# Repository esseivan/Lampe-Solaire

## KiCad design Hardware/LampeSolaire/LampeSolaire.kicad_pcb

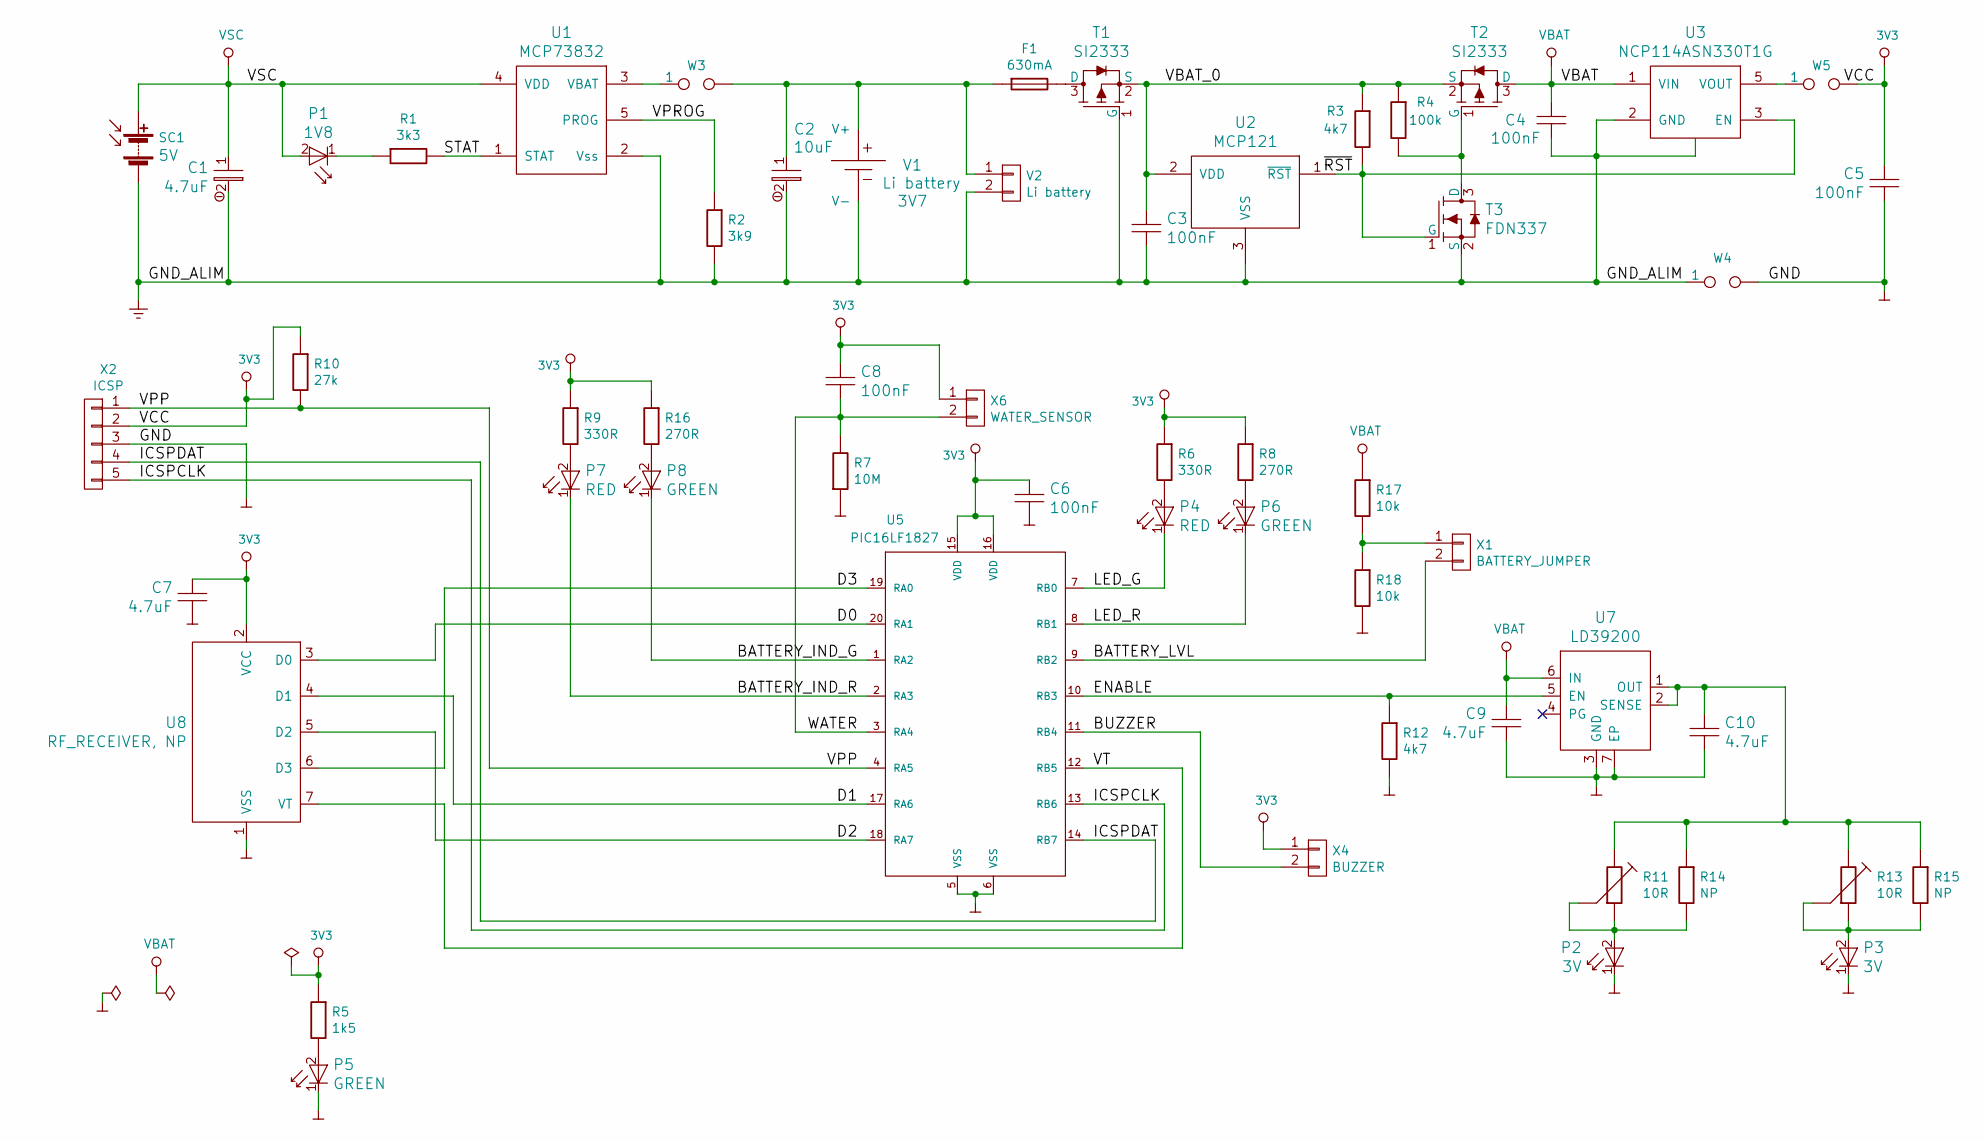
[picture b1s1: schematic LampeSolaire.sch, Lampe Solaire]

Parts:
C1, C7, C9, C10: 4.7uF; C_0805_HandSoldering
C2: 10uF; C_0805_HandSoldering
C3, C4, C5, C6, C8: 100nF; C_0805_HandSoldering
F1: 630mA; Fuse_SMD1206_HandSoldering
P1: 1V8; D_0603_HandSoldering
P2, P3: 3V; Pin_Header_Straight_1x02_Pitch2.54mm
P4, P7: RED; D_0603_HandSoldering
P5, P6, P8: GREEN; D_0603_HandSoldering
R1: 3k3; R_0805_HandSoldering
R2: 3k9; R_0805_HandSoldering
R3, R12: 4k7; R_0805_HandSoldering
R4: 100k; R_0805_HandSoldering
R5: 1k5; R_0805_HandSoldering
R6, R9: 330R; R_0805_HandSoldering
R7: 10M; R_0805_HandSoldering
R8, R16: 270R; R_0805_HandSoldering
R10: 27k; R_0805_HandSoldering
R11, R13: 10R; Potentiometer_Trimmer_Bourns_3006P
R14, R15: NP; R_0805_HandSoldering
R17, R18: 10k; R_0805_HandSoldering
SC1: Solar_Cells; Pin_Header_Straight_1x02_Pitch2.54mm; Voltage 5V
T1, T2: SI2333; SOT-23_Handsoldering
T3: FDN337; SOT-23_Handsoldering
U1: MCP73832; SOT-23-5_HandSoldering
U2: MCP121; SOT-23_Handsoldering
U3: NCP114ASN330T1G; TSOP-5
U5: PIC16LF1827; SSOP-20_5.3x7.2mm_Pitch0.65mm
U7: LD39200; DFN-6-1EP_3x3mm_Pitch0.95mm
U8: RF_RECEIVER, NP; RF_RECEIVER
V1: Li battery; 18650 Battery holder; Voltage 3V7
V2: Li battery; Pin_Header_Straight_1x02_Pitch2.54mm
W3, W4, W5: TEST_2P; Pin_Header_Straight_1x02_Pitch2.54mm
X1: BATTERY_JUMPER; Pin_Header_Straight_1x02_Pitch2.54mm
X2: ICSP; Pin_Header_Straight_1x05_Pitch2.54mm
X4: BUZZER; Pin_Header_Straight_1x02_Pitch2.54mm
X6: WATER_SENSOR; Pin_Header_Straight_1x02_Pitch2.54mm

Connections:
3V3: C5.1, C6.1, C7.1, C8.1, R5.2, R6.2, R8.2, R9.2, R10.2, R16.2, U5.15 (VDD), U5.16 (VDD), U8.2 (VCC), W5.2, X2.2, X4.1, X6.1
/BATTERY_IND_G: P8.1 (Cathode), U5.1 (RA2)
/BATTERY_IND_R: P7.1 (Cathode), U5.2 (RA3)
/BATTERY_LVL: U5.9 (RB2), X1.2
/BUZZER: U5.11 (RB4), X4.2
/D0: U5.20 (RA1), U8.3 (D0)
/D1: U5.17 (RA6), U8.4 (D1)
/D2: U5.18 (RA7), U8.5 (D2)
/D3: U5.19 (RA0), U8.6 (D3)
/ENABLE: R12.2, U5.10 (RB3), U7.5 (EN)
/ICSPCLK: U5.13 (RB6), X2.5
/ICSPDAT: U5.14 (RB7), X2.4
/LED_G: P4.1 (Cathode), U5.7 (RB0)
/LED_R: P6.1 (Cathode), U5.8 (RB1)
/STAT: R1.1, U1.1 (STAT)
/VBAT_0: C3.1, R3.2, R4.2, T1.2 (S), T2.2 (S), U2.2 (VDD)
/VPP: R10.1, U5.4 (RA5), X2.1
/VPROG: R2.2, U1.5 (PROG)
/VT: U5.12 (RB5), U8.7 (VT)
/WATER: C8.2, R7.1, U5.3 (RA4), X6.2
/~RST: R3.1, T3.1 (G), U2.1 (~RST), U3.3 (EN)
GND: C5.2, C6.2, C7.2, C9.2, C10.2, P2.1 (Cathode), P3.1 (Cathode), P5.1 (Cathode), R7.2, R12.1, R18.1, U5.5 (VSS), U5.6 (VSS), U7.3 (GND), U7.7 (EP), U8.1 (VSS), W4.2, X2.3
GND_ALIM: C1.2, C2.2, C3.2, C4.2, R2.1, SC1.2 (-), T1.1 (G), T3.2 (S), U1.2 (Vss), U2.3 (VSS), U3.2 (GND~), U3.4 (NC), V1.2 (V-), V2.2, W4.1
unnamed: C2.1, F1.2, V1.1 (V+), V2.1, W3.2
unnamed: C10.1, R11.1, R13.1, R14.2, R15.2, U7.1 (OUT), U7.2 (SENSE)
unnamed: F1.1, T1.3 (D)
unnamed: P1.1 (Cathode), R1.2
unnamed: P2.2 (Anode), R11.2, R11.3, R14.1
unnamed: P3.2 (Anode), R13.2, R13.3, R15.1
unnamed: P4.2 (Anode), R6.1
unnamed: P5.2 (Anode), R5.1
unnamed: P6.2 (Anode), R8.1
unnamed: P7.2 (Anode), R9.1
unnamed: P8.2 (Anode), R16.1
unnamed: R4.1, T2.1 (G), T3.3 (D)
unnamed: R17.1, R18.2, X1.1
unnamed: U1.3 (VBAT), W3.1
unnamed: U3.5 (VOUT), W5.1
VBAT: C4.1, C9.1, R17.2, T2.3 (D), U3.1 (VIN), U7.6 (IN)
VSC: C1.1, P1.2 (Anode), SC1.1 (+), U1.4 (VDD)

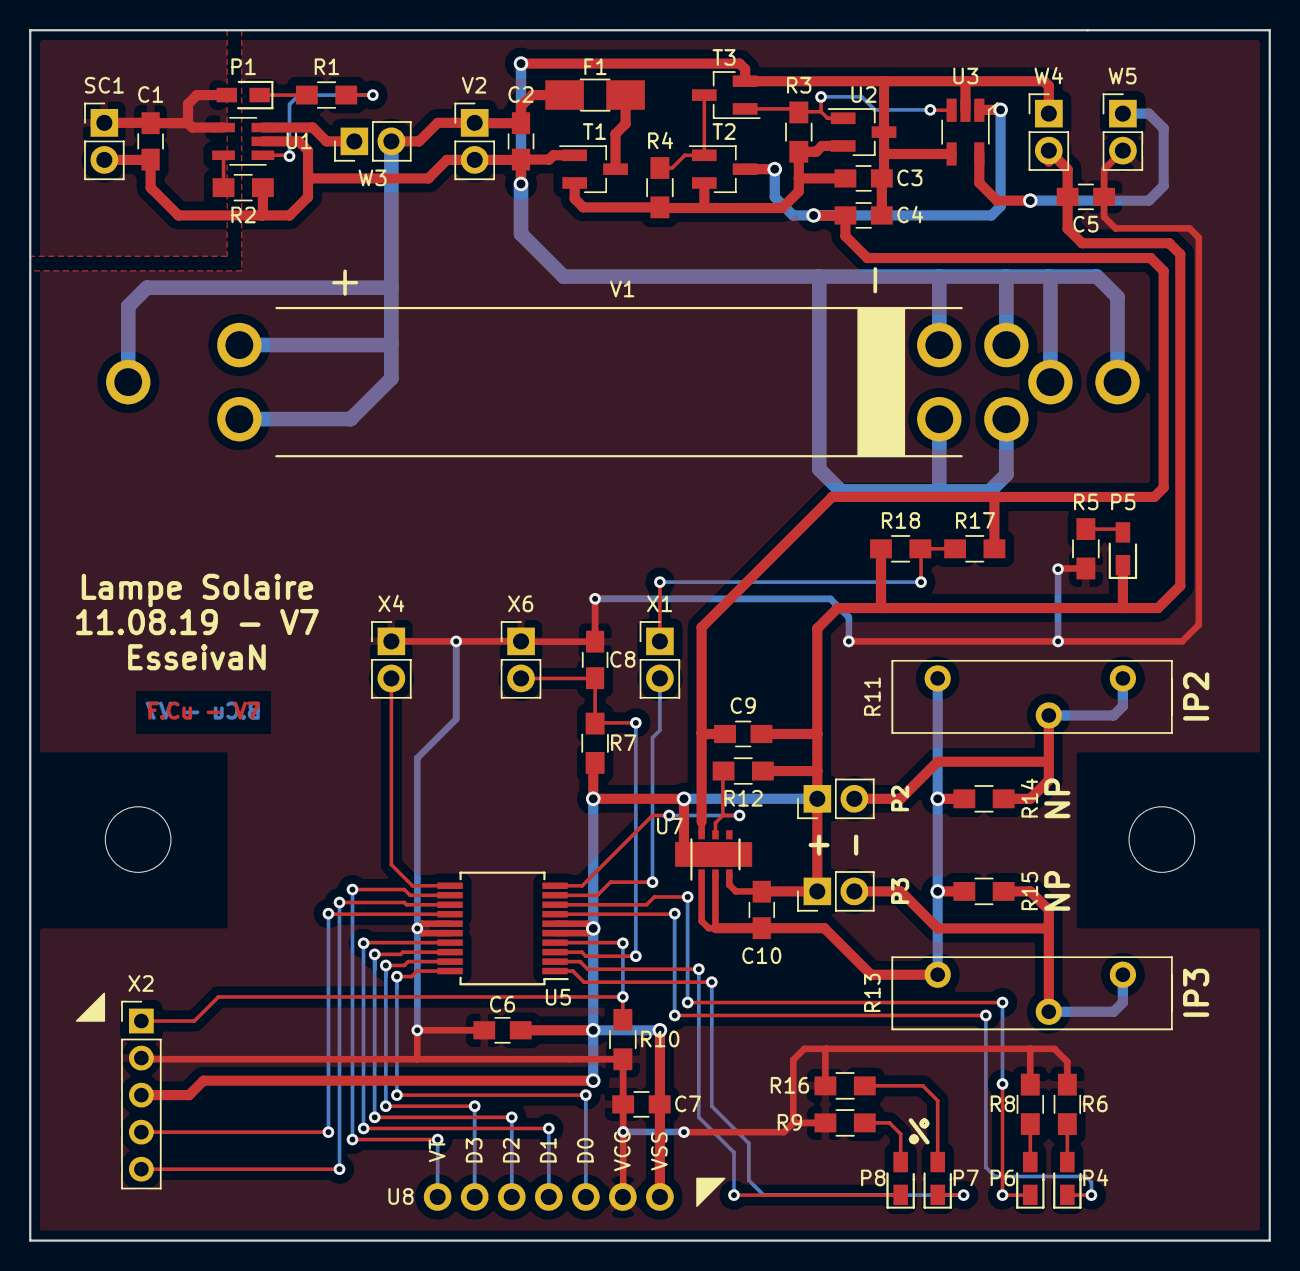
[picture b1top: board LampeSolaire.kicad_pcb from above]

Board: 2 copper layers, 85.0 x 83.0 mm, 58 parts (0 on the bottom side), 40 nets.

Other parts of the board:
PERC-4.5mm, PERC-4.5mm#2: PERC-4.5mm

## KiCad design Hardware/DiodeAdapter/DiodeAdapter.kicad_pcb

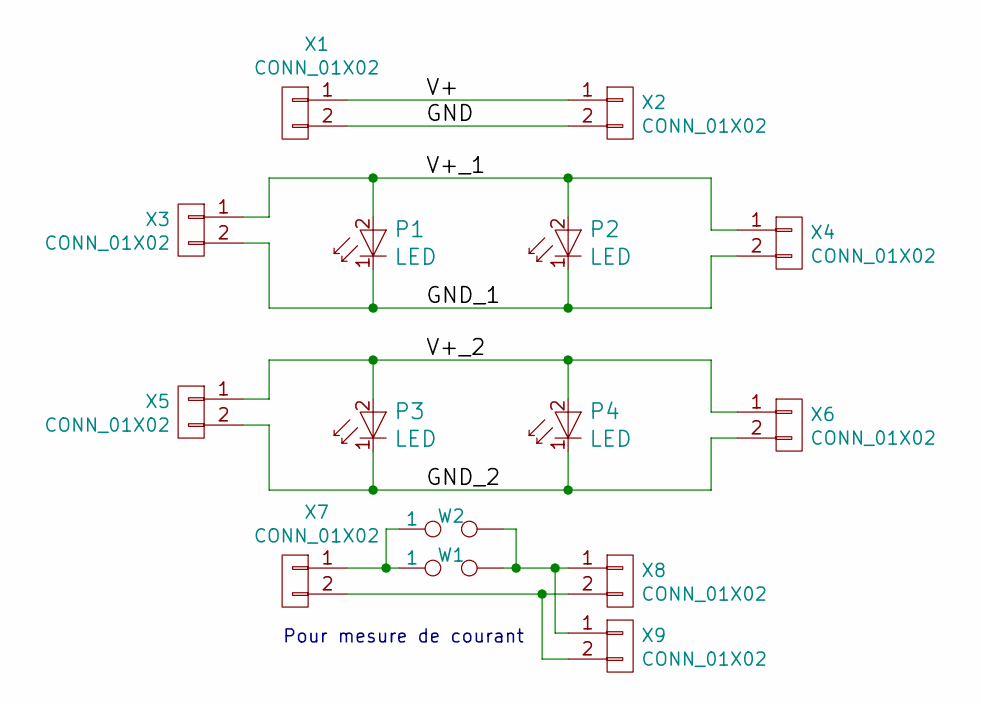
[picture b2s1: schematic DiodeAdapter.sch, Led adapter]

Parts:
P1, P3: LED; LED_LH351D
P2: LED; LED_LITTLE_STAR
P4: LED; LED_XQ_D
W1, W2: TEST_2P; Pin_Header_Straight_1x02_Pitch2.54mm
X1, X7: CONN_01X02; Pin_Header_Angled_1x02_Pitch2.54mm
X2, X3, X4, X5, X6, X9: CONN_01X02; Pin_Header_Straight_1x02_Pitch2.54mm
X8: CONN_01X02; Pin_Header_Angled_1x02_Pitch2.54mm_reverse

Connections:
/GND: X1.2, X2.2
/GND_1: P1.1 (Cathode), P2.1 (Cathode), X3.2, X4.2
/GND_2: P3.1 (Cathode), P4.1 (Cathode), X5.2, X6.2
/V+: X1.1, X2.1
/V+_1: P1.2 (Anode), P2.2 (Anode), X3.1, X4.1
/V+_2: P3.2 (Anode), P4.2 (Anode), X5.1, X6.1
unnamed: W1.1, W2.1, X7.1
unnamed: W1.2, W2.2, X8.1, X9.1
unnamed: X7.2, X8.2, X9.2

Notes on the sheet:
Pour mesure de courant

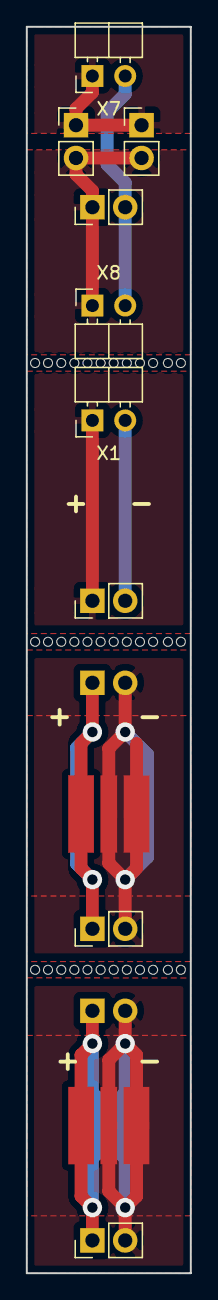
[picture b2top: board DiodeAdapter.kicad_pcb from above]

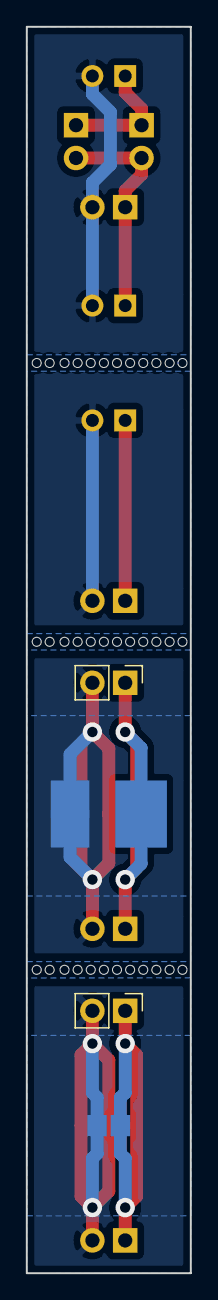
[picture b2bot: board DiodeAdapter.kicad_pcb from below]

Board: 2 copper layers, 12.7 x 96.5 mm, 15 parts (4 on the bottom side), 9 nets.

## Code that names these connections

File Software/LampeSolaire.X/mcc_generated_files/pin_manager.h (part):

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// get/set D3 aliases
#define D3_TRIS                 TRISAbits.TRISA0
#define D3_LAT                  LATAbits.LATA0
#define D3_PORT                 PORTAbits.RA0
#define D3_ANS                  ANSELAbits.ANSA0
#define D3_SetHigh()            do { LATAbits.LATA0 = 1; } while(0)
#define D3_SetLow()             do { LATAbits.LATA0 = 0; } while(0)
#define D3_Toggle()             do { LATAbits.LATA0 = ~LATAbits.LATA0; } while(0)
#define D3_GetValue()           PORTAbits.RA0
#define D3_SetDigitalInput()    do { TRISAbits.TRISA0 = 1; } while(0)
#define D3_SetDigitalOutput()   do { TRISAbits.TRISA0 = 0; } while(0)
#define D3_SetAnalogMode()      do { ANSELAbits.ANSA0 = 1; } while(0)
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// get/set D0 aliases
#define D0_TRIS                 TRISAbits.TRISA1
#define D0_LAT                  LATAbits.LATA1
#define D0_PORT                 PORTAbits.RA1
#define D0_ANS                  ANSELAbits.ANSA1
#define D0_SetHigh()            do { LATAbits.LATA1 = 1; } while(0)
#define D0_SetLow()             do { LATAbits.LATA1 = 0; } while(0)
#define D0_Toggle()             do { LATAbits.LATA1 = ~LATAbits.LATA1; } while(0)
#define D0_GetValue()           PORTAbits.RA1
#define D0_SetDigitalInput()    do { TRISAbits.TRISA1 = 1; } while(0)
#define D0_SetDigitalOutput()   do { TRISAbits.TRISA1 = 0; } while(0)
#define D0_SetAnalogMode()      do { ANSELAbits.ANSA1 = 1; } while(0)
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// get/set BATTERY_IND_G aliases
#define BATTERY_IND_G_TRIS                 TRISAbits.TRISA2
#define BATTERY_IND_G_LAT                  LATAbits.LATA2
#define BATTERY_IND_G_PORT                 PORTAbits.RA2
#define BATTERY_IND_G_ANS                  ANSELAbits.ANSA2
#define BATTERY_IND_G_SetHigh()            do { LATAbits.LATA2 = 1; } while(0)
#define BATTERY_IND_G_SetLow()             do { LATAbits.LATA2 = 0; } while(0)
#define BATTERY_IND_G_Toggle()             do { LATAbits.LATA2 = ~LATAbits.LATA2; } while(0)
#define BATTERY_IND_G_GetValue()           PORTAbits.RA2
#define BATTERY_IND_G_SetDigitalInput()    do { TRISAbits.TRISA2 = 1; } while(0)
#define BATTERY_IND_G_SetDigitalOutput()   do { TRISAbits.TRISA2 = 0; } while(0)
#define BATTERY_IND_G_SetAnalogMode()      do { ANSELAbits.ANSA2 = 1; } while(0)
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// get/set BATTERY_IND_R aliases
#define BATTERY_IND_R_TRIS                 TRISAbits.TRISA3
#define BATTERY_IND_R_LAT                  LATAbits.LATA3
#define BATTERY_IND_R_PORT                 PORTAbits.RA3
#define BATTERY_IND_R_ANS                  ANSELAbits.ANSA3
#define BATTERY_IND_R_SetHigh()            do { LATAbits.LATA3 = 1; } while(0)
#define BATTERY_IND_R_SetLow()             do { LATAbits.LATA3 = 0; } while(0)
#define BATTERY_IND_R_Toggle()             do { LATAbits.LATA3 = ~LATAbits.LATA3; } while(0)
#define BATTERY_IND_R_GetValue()           PORTAbits.RA3
#define BATTERY_IND_R_SetDigitalInput()    do { TRISAbits.TRISA3 = 1; } while(0)
#define BATTERY_IND_R_SetDigitalOutput()   do { TRISAbits.TRISA3 = 0; } while(0)
#define BATTERY_IND_R_SetAnalogMode()      do { ANSELAbits.ANSA3 = 1; } while(0)
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// get/set WATER aliases
#define WATER_TRIS                 TRISAbits.TRISA4
#define WATER_LAT                  LATAbits.LATA4
#define WATER_PORT                 PORTAbits.RA4
#define WATER_ANS                  ANSELAbits.ANSA4
#define WATER_SetHigh()            do { LATAbits.LATA4 = 1; } while(0)
#define WATER_SetLow()             do { LATAbits.LATA4 = 0; } while(0)
#define WATER_Toggle()             do { LATAbits.LATA4 = ~LATAbits.LATA4; } while(0)
#define WATER_GetValue()           PORTAbits.RA4
#define WATER_SetDigitalInput()    do { TRISAbits.TRISA4 = 1; } while(0)
#define WATER_SetDigitalOutput()   do { TRISAbits.TRISA4 = 0; } while(0)
#define WATER_SetAnalogMode()      do { ANSELAbits.ANSA4 = 1; } while(0)
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// get/set D1 aliases
#define D1_TRIS                 TRISAbits.TRISA6
#define D1_LAT                  LATAbits.LATA6
#define D1_PORT                 PORTAbits.RA6
#define D1_SetHigh()            do { LATAbits.LATA6 = 1; } while(0)
#define D1_SetLow()             do { LATAbits.LATA6 = 0; } while(0)
#define D1_Toggle()             do { LATAbits.LATA6 = ~LATAbits.LATA6; } while(0)
#define D1_GetValue()           PORTAbits.RA6
#define D1_SetDigitalInput()    do { TRISAbits.TRISA6 = 1; } while(0)
#define D1_SetDigitalOutput()   do { TRISAbits.TRISA6 = 0; } while(0)

// get/set D2 aliases
#define D2_TRIS                 TRISAbits.TRISA7
#define D2_LAT                  LATAbits.LATA7
#define D2_PORT                 PORTAbits.RA7
#define D2_SetHigh()            do { LATAbits.LATA7 = 1; } while(0)
#define D2_SetLow()             do { LATAbits.LATA7 = 0; } while(0)
#define D2_Toggle()             do { LATAbits.LATA7 = ~LATAbits.LATA7; } while(0)
#define D2_GetValue()           PORTAbits.RA7
#define D2_SetDigitalInput()    do { TRISAbits.TRISA7 = 1; } while(0)
#define D2_SetDigitalOutput()   do { TRISAbits.TRISA7 = 0; } while(0)

// get/set LED_R aliases
#define LED_R_TRIS                 TRISBbits.TRISB0
#define LED_R_LAT                  LATBbits.LATB0
#define LED_R_PORT                 PORTBbits.RB0
#define LED_R_WPU                  WPUBbits.WPUB0
#define LED_R_SetOff()            do { LATBbits.LATB0 = 1; } while(0)
#define LED_R_SetOn()             do { LATBbits.LATB0 = 0; } while(0)
#define LED_R_Toggle()             do { LATBbits.LATB0 = ~LATBbits.LATB0; } while(0)
#define LED_R_GetValue()           PORTBbits.RB0
#define LED_R_SetDigitalInput()    do { TRISBbits.TRISB0 = 1; } while(0)
#define LED_R_SetDigitalOutput()   do { TRISBbits.TRISB0 = 0; } while(0)
#define LED_R_SetPullup()          do { WPUBbits.WPUB0 = 1; } while(0)
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// get/set LED_G aliases
#define LED_G_TRIS                 TRISBbits.TRISB1
#define LED_G_LAT                  LATBbits.LATB1
#define LED_G_PORT                 PORTBbits.RB1
#define LED_G_WPU                  WPUBbits.WPUB1
#define LED_G_ANS                  ANSELBbits.ANSB1
#define LED_G_SetOff()            do { LATBbits.LATB1 = 1; } while(0)
#define LED_G_SetOn()             do { LATBbits.LATB1 = 0; } while(0)
#define LED_G_Toggle()             do { LATBbits.LATB1 = ~LATBbits.LATB1; } while(0)
#define LED_G_GetValue()           PORTBbits.RB1
#define LED_G_SetDigitalInput()    do { TRISBbits.TRISB1 = 1; } while(0)
#define LED_G_SetDigitalOutput()   do { TRISBbits.TRISB1 = 0; } while(0)
#define LED_G_SetPullup()          do { WPUBbits.WPUB1 = 1; } while(0)
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// get/set BATTERY_LVL aliases
#define BATTERY_LVL_TRIS                 TRISBbits.TRISB2
#define BATTERY_LVL_LAT                  LATBbits.LATB2
#define BATTERY_LVL_PORT                 PORTBbits.RB2
#define BATTERY_LVL_WPU                  WPUBbits.WPUB2
#define BATTERY_LVL_ANS                  ANSELBbits.ANSB2
#define BATTERY_LVL_SetHigh()            do { LATBbits.LATB2 = 1; } while(0)
#define BATTERY_LVL_SetLow()             do { LATBbits.LATB2 = 0; } while(0)
#define BATTERY_LVL_Toggle()             do { LATBbits.LATB2 = ~LATBbits.LATB2; } while(0)
#define BATTERY_LVL_GetValue()           PORTBbits.RB2
#define BATTERY_LVL_SetDigitalInput()    do { TRISBbits.TRISB2 = 1; } while(0)
#define BATTERY_LVL_SetDigitalOutput()   do { TRISBbits.TRISB2 = 0; } while(0)
#define BATTERY_LVL_SetPullup()          do { WPUBbits.WPUB2 = 1; } while(0)
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// get/set ENABLE aliases
#define ENABLE_TRIS                 TRISBbits.TRISB3
#define ENABLE_LAT                  LATBbits.LATB3
#define ENABLE_PORT                 PORTBbits.RB3
#define ENABLE_WPU                  WPUBbits.WPUB3
#define ENABLE_ANS                  ANSELBbits.ANSB3
#define ENABLE_SetHigh()            do { LATBbits.LATB3 = 1; } while(0)
#define ENABLE_SetLow()             do { LATBbits.LATB3 = 0; } while(0)
#define ENABLE_Toggle()             do { LATBbits.LATB3 = ~LATBbits.LATB3; } while(0)
#define ENABLE_GetValue()           PORTBbits.RB3
#define ENABLE_SetDigitalInput()    do { TRISBbits.TRISB3 = 1; } while(0)
#define ENABLE_SetDigitalOutput()   do { TRISBbits.TRISB3 = 0; } while(0)
#define ENABLE_SetPullup()          do { WPUBbits.WPUB3 = 1; } while(0)
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// get/set BUZZER aliases
#define BUZZER_TRIS                 TRISBbits.TRISB4
#define BUZZER_LAT                  LATBbits.LATB4
#define BUZZER_PORT                 PORTBbits.RB4
#define BUZZER_WPU                  WPUBbits.WPUB4
#define BUZZER_ANS                  ANSELBbits.ANSB4
#define BUZZER_SetHigh()            do { LATBbits.LATB4 = 1; } while(0)
#define BUZZER_SetLow()             do { LATBbits.LATB4 = 0; } while(0)
#define BUZZER_Toggle()             do { LATBbits.LATB4 = ~LATBbits.LATB4; } while(0)
#define BUZZER_GetValue()           PORTBbits.RB4
#define BUZZER_SetDigitalInput()    do { TRISBbits.TRISB4 = 1; } while(0)
#define BUZZER_SetDigitalOutput()   do { TRISBbits.TRISB4 = 0; } while(0)
#define BUZZER_SetPullup()          do { WPUBbits.WPUB4 = 1; } while(0)
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// get/set VT aliases
#define VT_TRIS                 TRISBbits.TRISB5
#define VT_LAT                  LATBbits.LATB5
#define VT_PORT                 PORTBbits.RB5
#define VT_WPU                  WPUBbits.WPUB5
#define VT_ANS                  ANSELBbits.ANSB5
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
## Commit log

2019-01-30 Initial upload v2
2019-01-30 Fixed bug from switch kicad 4 to 5
2019-01-30 Version 4
    Nouveau PCB, modifications diverses au schéma
2019-04-23 Cleanup
2019-04-23 Updated rf module
    Uses now transceiver 860MHz
2019-04-25 Schematic v5 and PCB v5.1
2019-04-25 To remap because of error on ssop mcu
2019-04-26 Remap complete
    Commit before cleanup and size reducing
2019-04-26 Cleanup done
2019-04-26 Ready for silks cleanup
2019-05-01 V5 Complete
2019-05-08 don't ignore mplab
2019-05-08 Merged MCC
2019-05-08 software build
2019-06-17 Update for next version
2019-06-17 Update 2
2019-06-23 preparation for v6
2019-06-24 Version 6 final
2019-07-04 Software update
2019-07-08 OOK kinda working
2019-07-08 ook *kinda working again
    Values not good, reception ok
2019-07-30 trying to get correct data
2019-08-08 first upgrade for v7
2019-08-11 Waiting for last check

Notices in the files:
Software/LampeSolaire.X/mcc_generated_files/pin_manager.h:
(c) 2018 Microchip Technology Inc. and its subsidiaries.
